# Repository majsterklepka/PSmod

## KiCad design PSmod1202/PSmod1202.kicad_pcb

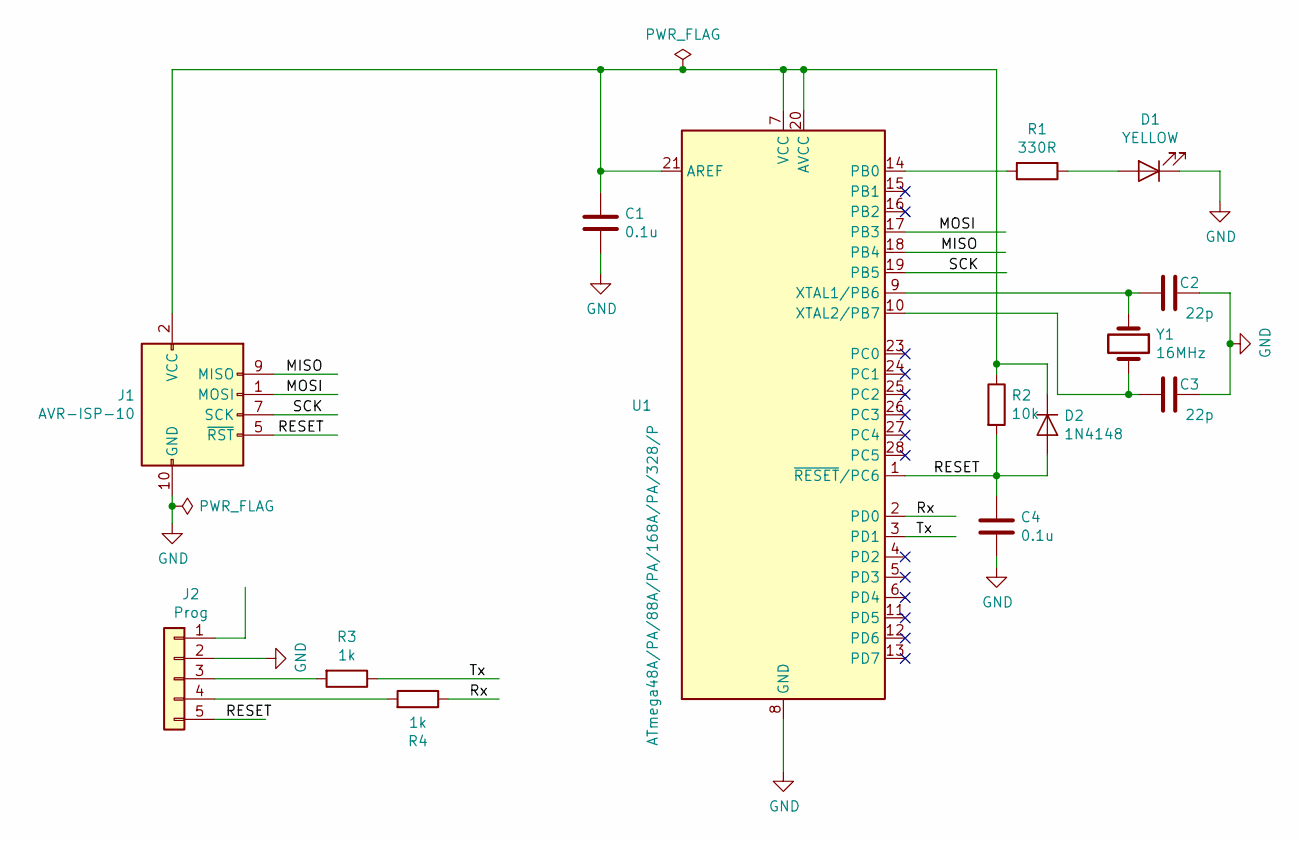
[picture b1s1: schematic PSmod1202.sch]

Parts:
C1, C4: 0.1u; C_Rect_L7.0mm_W2.0mm_P5.00mm
C2, C3: 22p; C_Disc_D4.3mm_W1.9mm_P5.00mm
D1: YELLOW; LED_D3.0mm
D2: 1N4148; D_DO-35_SOD27_P7.62mm_Horizontal
J1: AVR-ISP-10; IDC-Header_2x05_P2.54mm_Vertical
J2: Prog; PinHeader_1x05_P2.54mm_Vertical
R1: 330R; R_Axial_DIN0207_L6.3mm_D2.5mm_P7.62mm_Horizontal
R2: 10k; R_Axial_DIN0207_L6.3mm_D2.5mm_P7.62mm_Horizontal
R3, R4: 1k; R_Axial_DIN0207_L6.3mm_D2.5mm_P7.62mm_Horizontal
U1: ATmega48A/PA/88A/PA/168A/PA/328/P; DIP_Socket-28_W6.9_W7.62_W10.16_W12.7_W13.5_3M_228-4817-00-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
Y1: 16MHz; Crystal_HC49-U_Vertical

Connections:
/MISO: J1.9 (MISO), U1.18 (PB4)
/MOSI: J1.1 (MOSI), U1.17 (PB3)
/RESET: C4.1, D2.2 (A), J1.5 (~RST), J2.5, R2.2, U1.1 (~RESET~/PC6)
/Rx: R4.1, U1.2 (PD0)
/SCK: J1.7 (SCK), U1.19 (PB5)
/Tx: R3.1, U1.3 (PD1)
GND: C1.2, C2.1, C3.1, C4.2, D1.1 (K), J1.4 (GND), J1.6 (GND), J1.8 (GND), J1.10 (GND), J2.2, U1.8 (GND), U1.22 (GND)
unnamed: C1.1, D2.1 (K), J1.2 (VCC), R2.1, U1.7 (VCC), U1.20 (AVCC), U1.21 (AREF)
unnamed: C2.2, U1.9 (XTAL1/PB6), Y1.1
unnamed: C3.2, U1.10 (XTAL2/PB7), Y1.2
unnamed: D1.2 (A), R1.1
unnamed: J2.3, R3.2
unnamed: J2.4, R4.2
unnamed: R1.2, U1.14 (PB0)

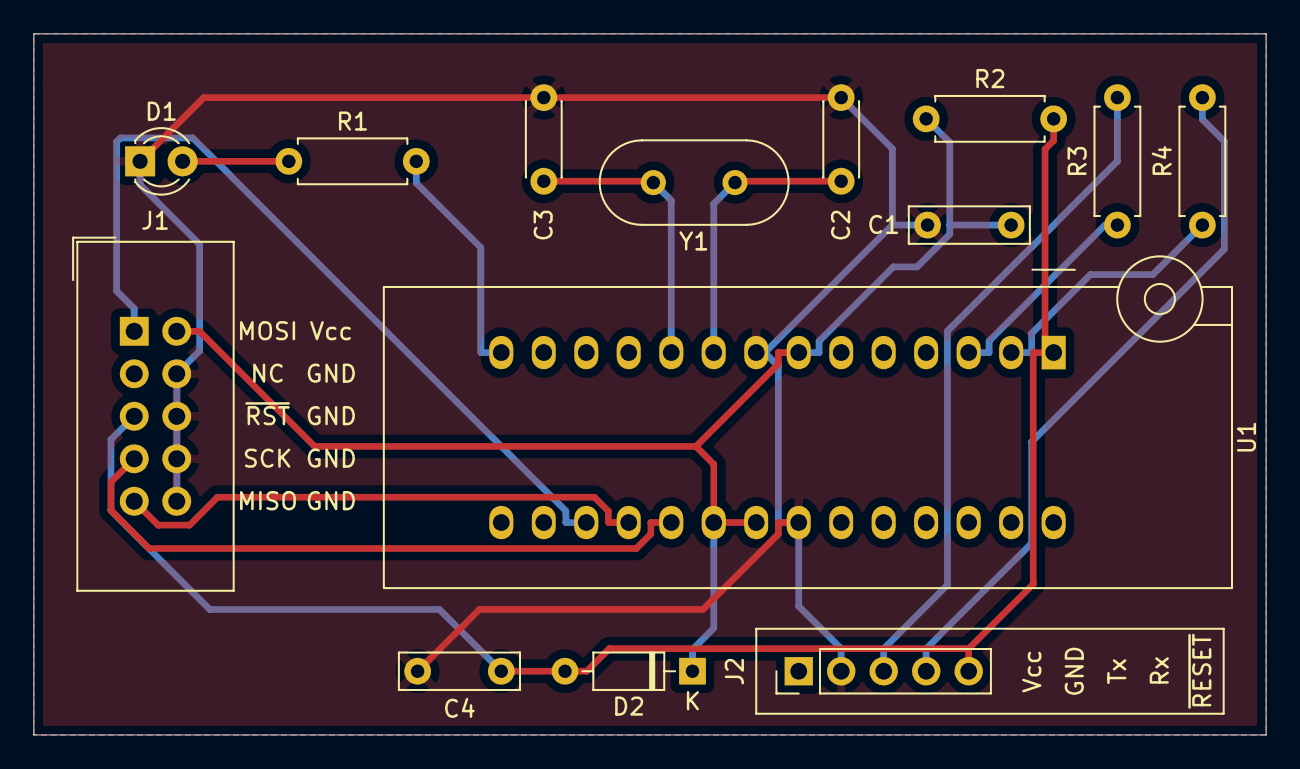
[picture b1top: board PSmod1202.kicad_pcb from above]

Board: 2 copper layers, 73.7 x 41.9 mm, 14 parts (0 on the bottom side), 14 nets.

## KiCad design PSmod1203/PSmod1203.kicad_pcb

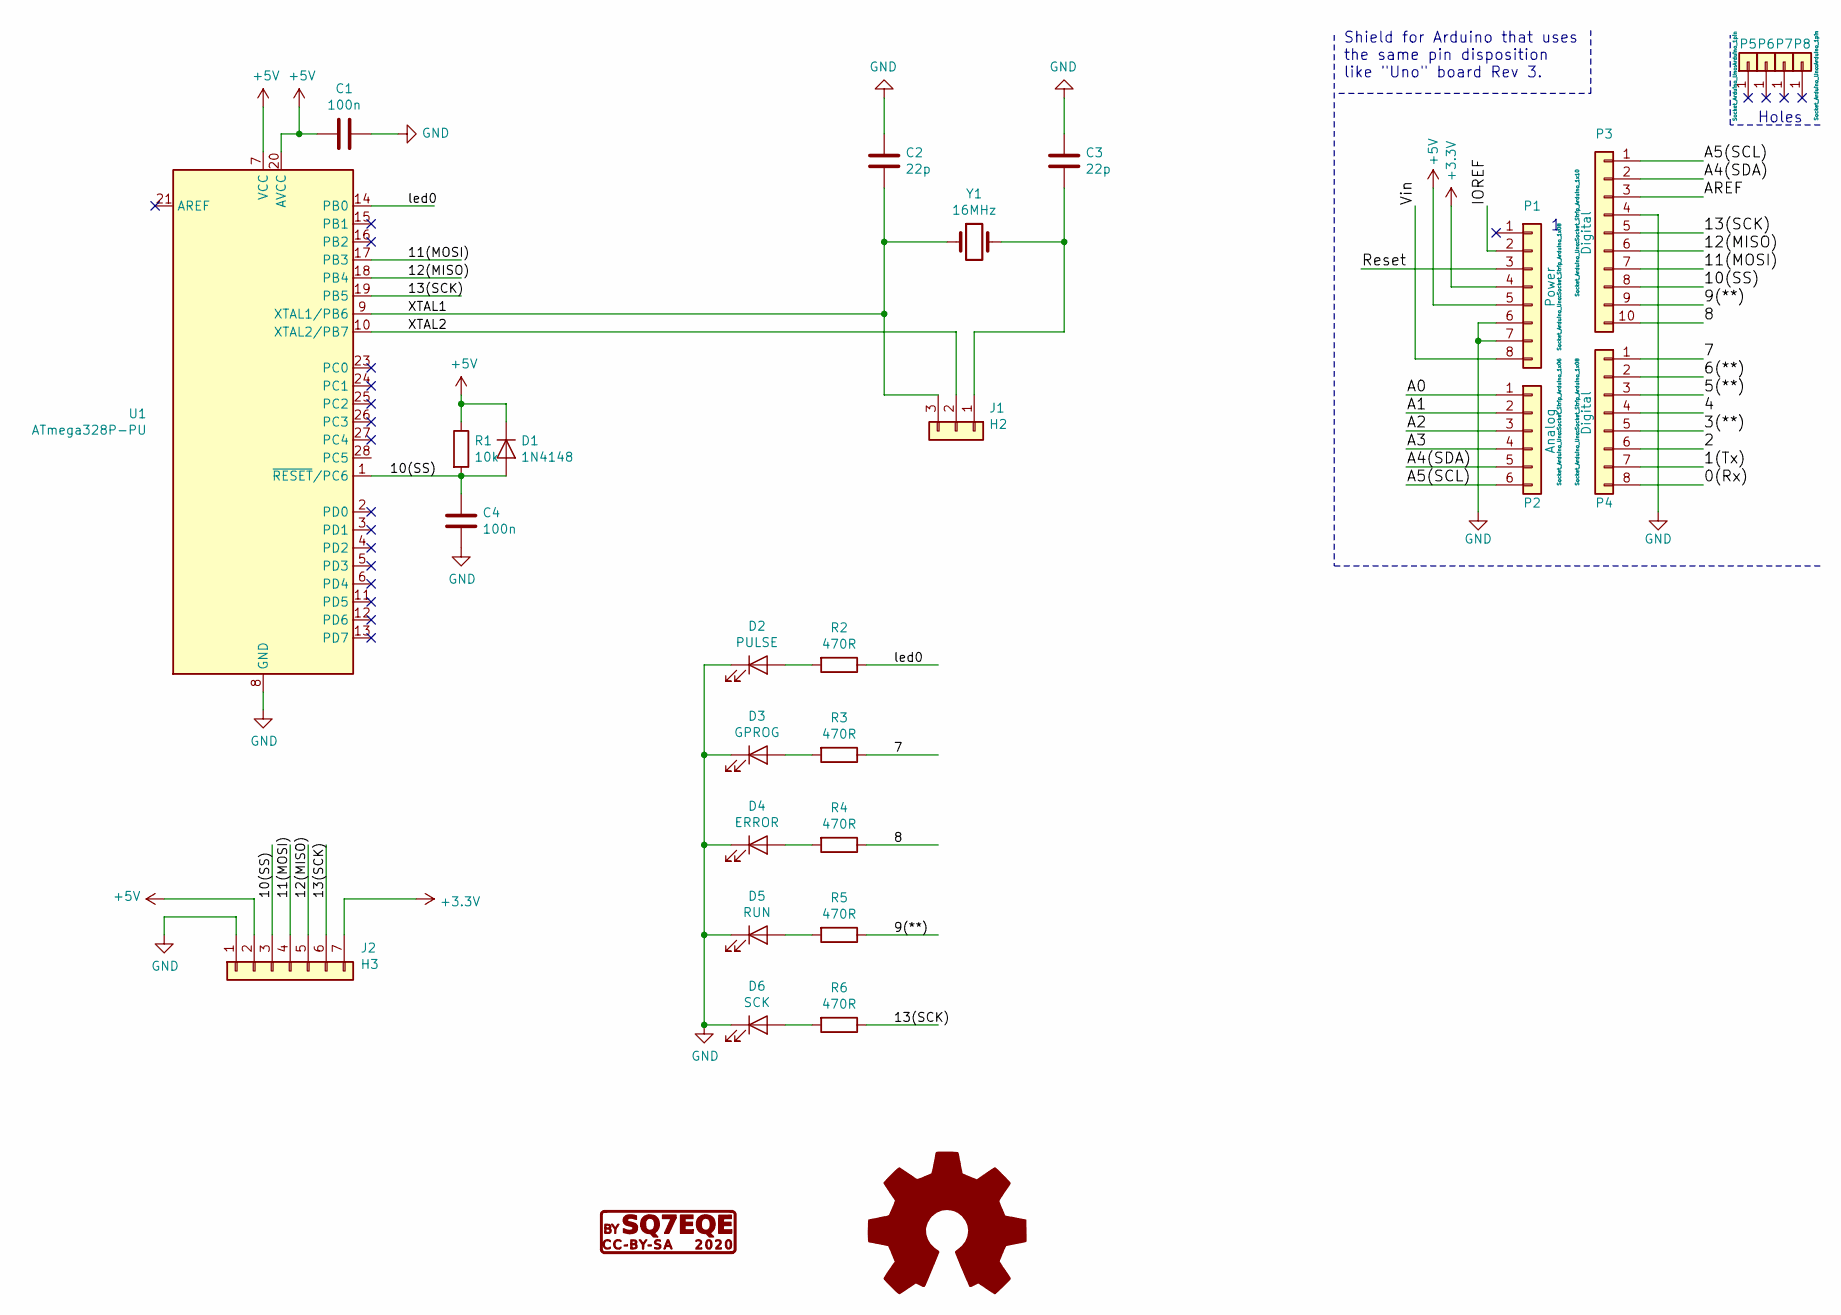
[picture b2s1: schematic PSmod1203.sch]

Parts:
C1, C4: 100n; C_Rect_L7.0mm_W2.0mm_P5.00mm
C2, C3: 22p; C_Disc_D4.3mm_W1.9mm_P5.00mm
D1: 1N4148; D_DO-35_SOD27_P7.62mm_Horizontal
D2: PULSE; LED_D3.0mm
D3: GPROG; LED_D3.0mm
D4: ERROR; LED_D3.0mm
D5: RUN; LED_D3.0mm
D6: SCK; LED_D3.0mm
G1: CC-BY-SA; cc-by-sa
J1: H2; PinHeader_1x03_P2.54mm_Vertical
J2: H3; PinHeader_1x07_P2.54mm_Vertical
LOGO1: Logo_Open_Hardware_Large; OSHW-Logo2_9.8x8mm_SilkScreen
P1: Power; Socket_Strip_Arduino_1x08
P2: Analog; Socket_Strip_Arduino_1x06
P3: Digital; Socket_Strip_Arduino_1x10
P4: Digital; Socket_Strip_Arduino_1x08
P5, P6, P7, P8: CONN_01X01; Arduino_1pin
R1: 10k; R_Axial_DIN0207_L6.3mm_D2.5mm_P7.62mm_Horizontal
R2, R3, R4, R5, R6: 470R; R_Axial_DIN0207_L6.3mm_D2.5mm_P7.62mm_Horizontal
U1: ATmega328P-PU; DIP_Socket-28_W6.9_W7.62_W10.16_W12.7_W13.5_3M_228-4817-00-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
Y1: 16MHz; Crystal_HC49-4H_Vertical

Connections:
+3V3: J2.7, P1.4
+5V: C1.2, D1.1 (K), J2.2, P1.5, R1.1, U1.7 (VCC), U1.20 (AVCC)
/0(Rx): P4.8
/1(Tx): P4.7
/2: P4.6
/3(**): P4.5
/4: P4.4
/5(**): P4.3
/6(**): P4.2
/7: P4.1, R3.1
/8: P3.10, R4.1
/9(**): P3.9, R5.1
/10(SS): C4.1, D1.2 (A), J2.3, P3.8, R1.2, U1.1 (~RESET~/PC6)
/11(MOSI): J2.4, P3.7, U1.17 (PB3)
/12(MISO): J2.5, P3.6, U1.18 (PB4)
/13(SCK): J2.6, P3.5, R6.1, U1.19 (PB5)
/A0: P2.1
/A1: P2.2
/A2: P2.3
/A3: P2.4
/A4(SDA): P2.5, P3.2
/A5(SCL): P2.6, P3.1
/AREF: P3.3
/IOREF: P1.2
/Reset: P1.3
/Vin: P1.8
/XTAL1: C2.2, J1.3, U1.9 (XTAL1/PB6), Y1.1
/XTAL2: J1.2, U1.10 (XTAL2/PB7)
/led0: R2.1, U1.14 (PB0)
GND: C1.1, C2.1, C3.1, C4.2, D2.1 (K), D3.1 (K), D4.1 (K), D5.1 (K), D6.1 (K), J2.1, P1.6, P1.7, P3.4, U1.8 (GND), U1.22 (GND)
unnamed: C3.2, J1.1, Y1.2
unnamed: D2.2 (A), R2.2
unnamed: D3.2 (A), R3.2
unnamed: D4.2 (A), R4.2
unnamed: D5.2 (A), R5.2
unnamed: D6.2 (A), R6.2

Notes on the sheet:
Holes
Shield for Arduino that uses the same pin disposition like "Uno" board Rev 3.

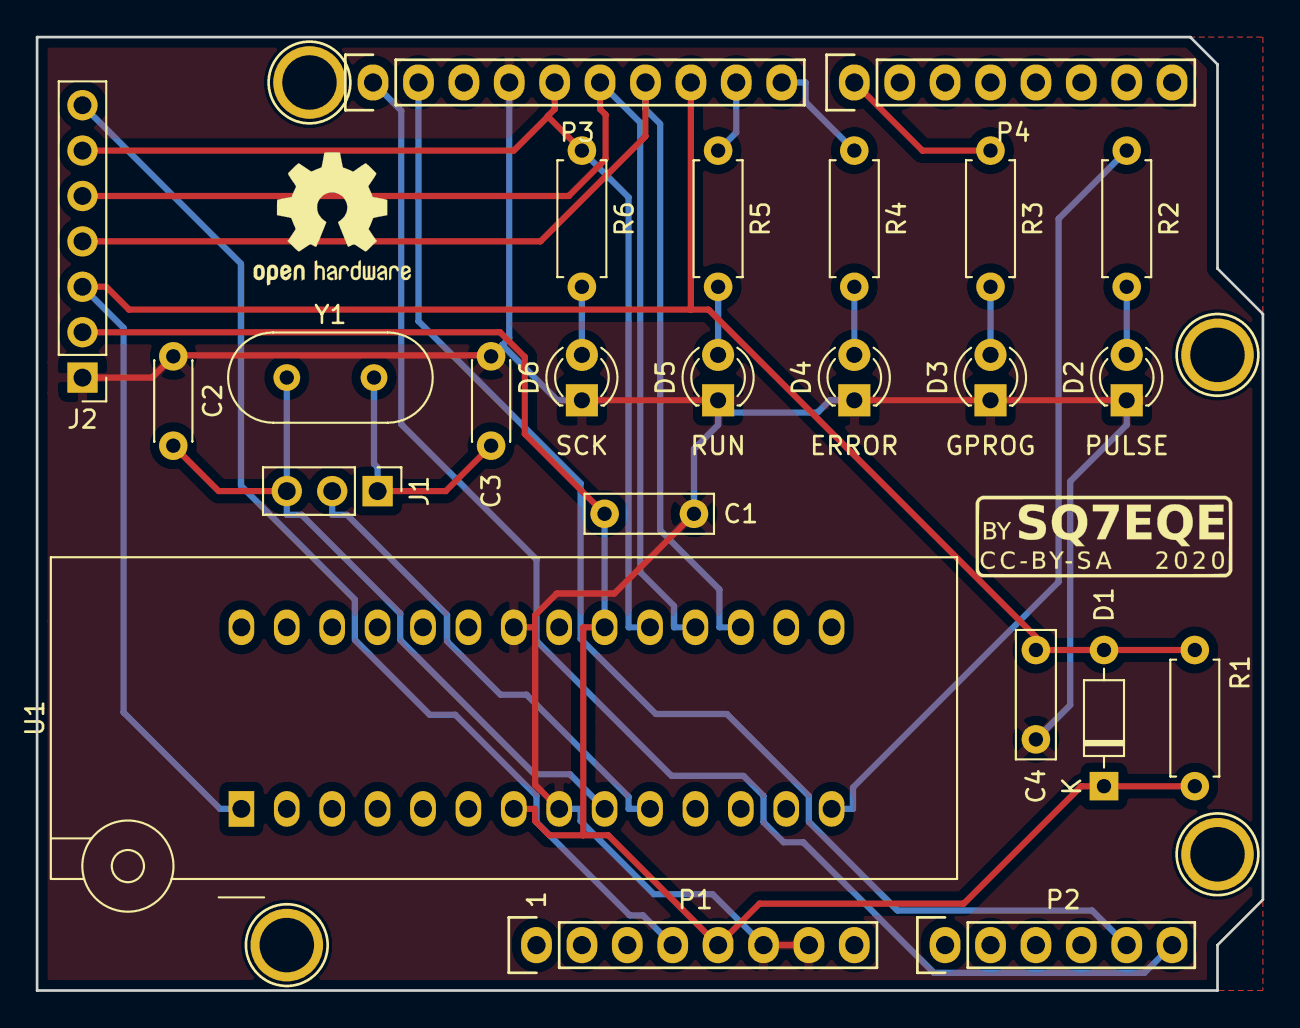
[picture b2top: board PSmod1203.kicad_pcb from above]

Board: 2 copper layers, 68.6 x 53.3 mm, 30 parts (0 on the bottom side), 21 nets.

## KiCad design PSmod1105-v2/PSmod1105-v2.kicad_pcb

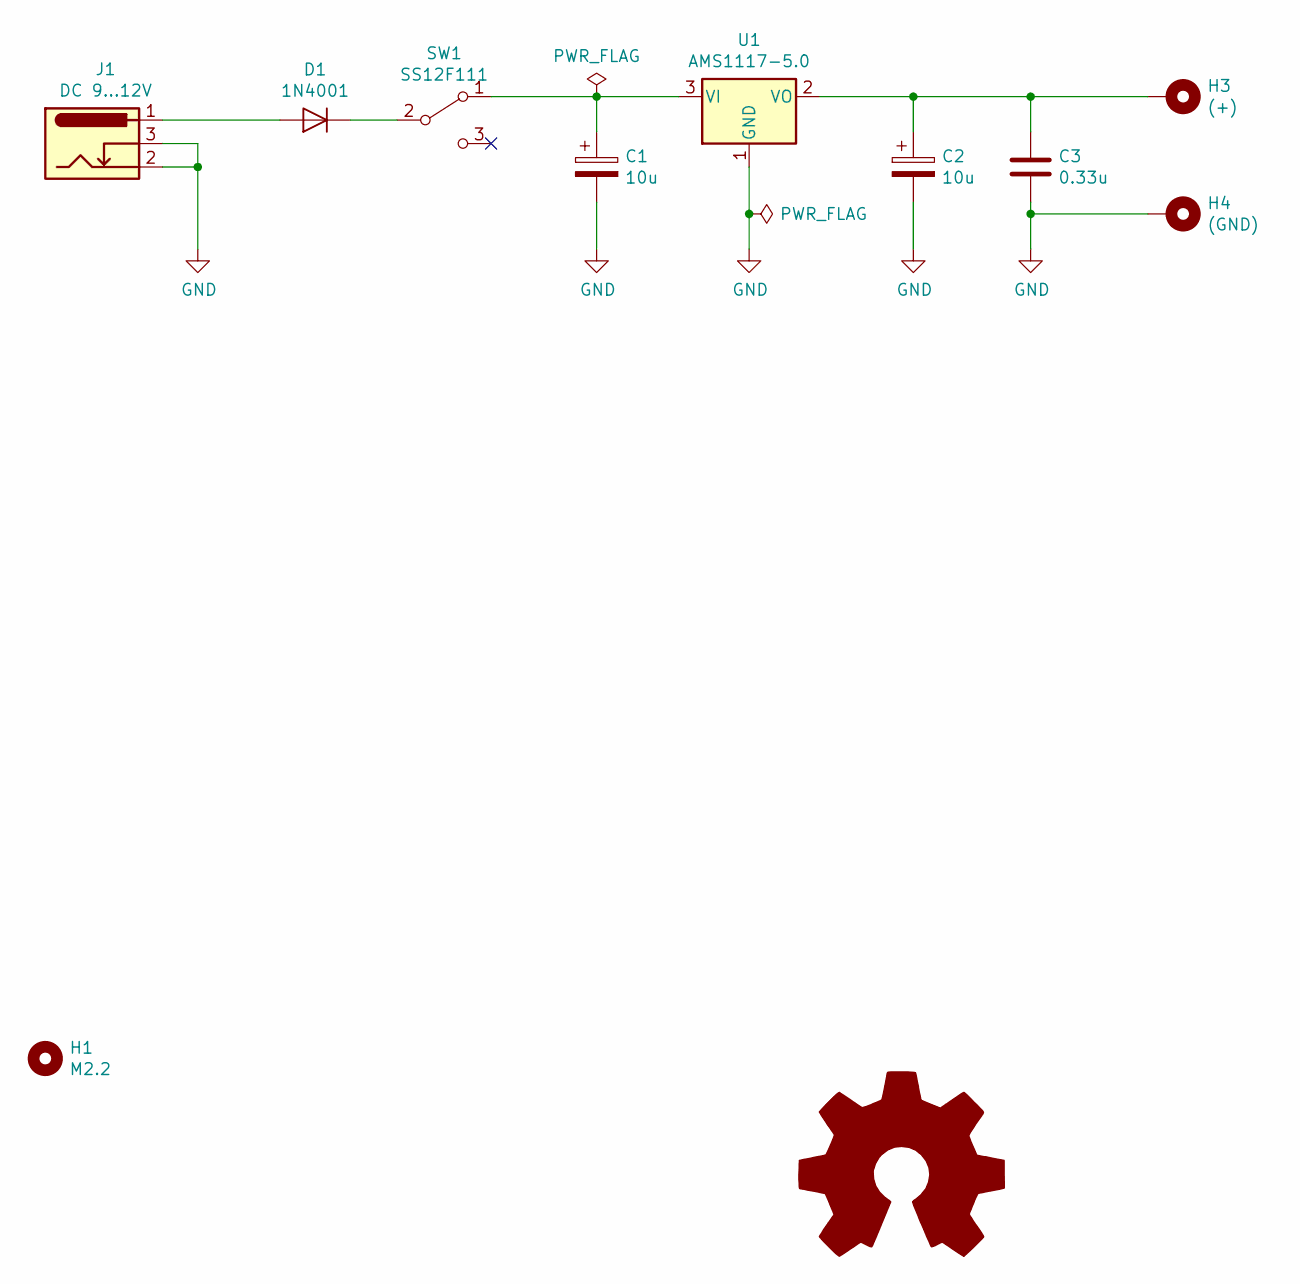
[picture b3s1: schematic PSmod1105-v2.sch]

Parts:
C1, C2: 10u; CP_Radial_D5.0mm_P2.50mm
C3: 0.33u; C_Rect_L7.0mm_W2.0mm_P5.00mm
D1: 1N4001; D_DO-41_SOD81_P10.16mm_Horizontal
H1: M2.2; MountingHole_2.2mm_M2_DIN965
H3: (+); MountingHole_2.2mm_M2_DIN965_Pad
H4: (GND); MountingHole_2.2mm_M2_DIN965_Pad
J1: DC 9...12V; NRB21R
LOGO1: Logo_Open_Hardware_Large; OSHW-Logo2_9.8x8mm_SilkScreen
SW1: SS12F111
U1: AMS1117-5.0; SOT-223-3_TabPin2

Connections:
GND: C1.2, C2.2, C3.2, H4.1, J1.2, J1.3, U1.1 (GND)
unnamed: C1.1, SW1.1 (A), U1.3 (VI)
unnamed: C2.1, C3.1, H3.1, U1.2 (VO)
unnamed: D1.1 (K), SW1.2 (B)
unnamed: D1.2 (A), J1.1

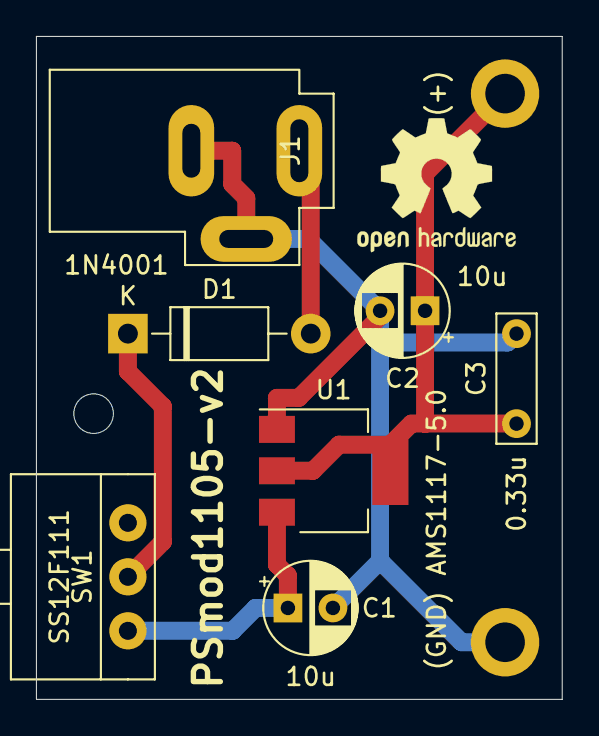
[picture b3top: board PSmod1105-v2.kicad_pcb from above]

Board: 2 copper layers, 29.2 x 36.8 mm, 11 parts (0 on the bottom side), 5 nets.

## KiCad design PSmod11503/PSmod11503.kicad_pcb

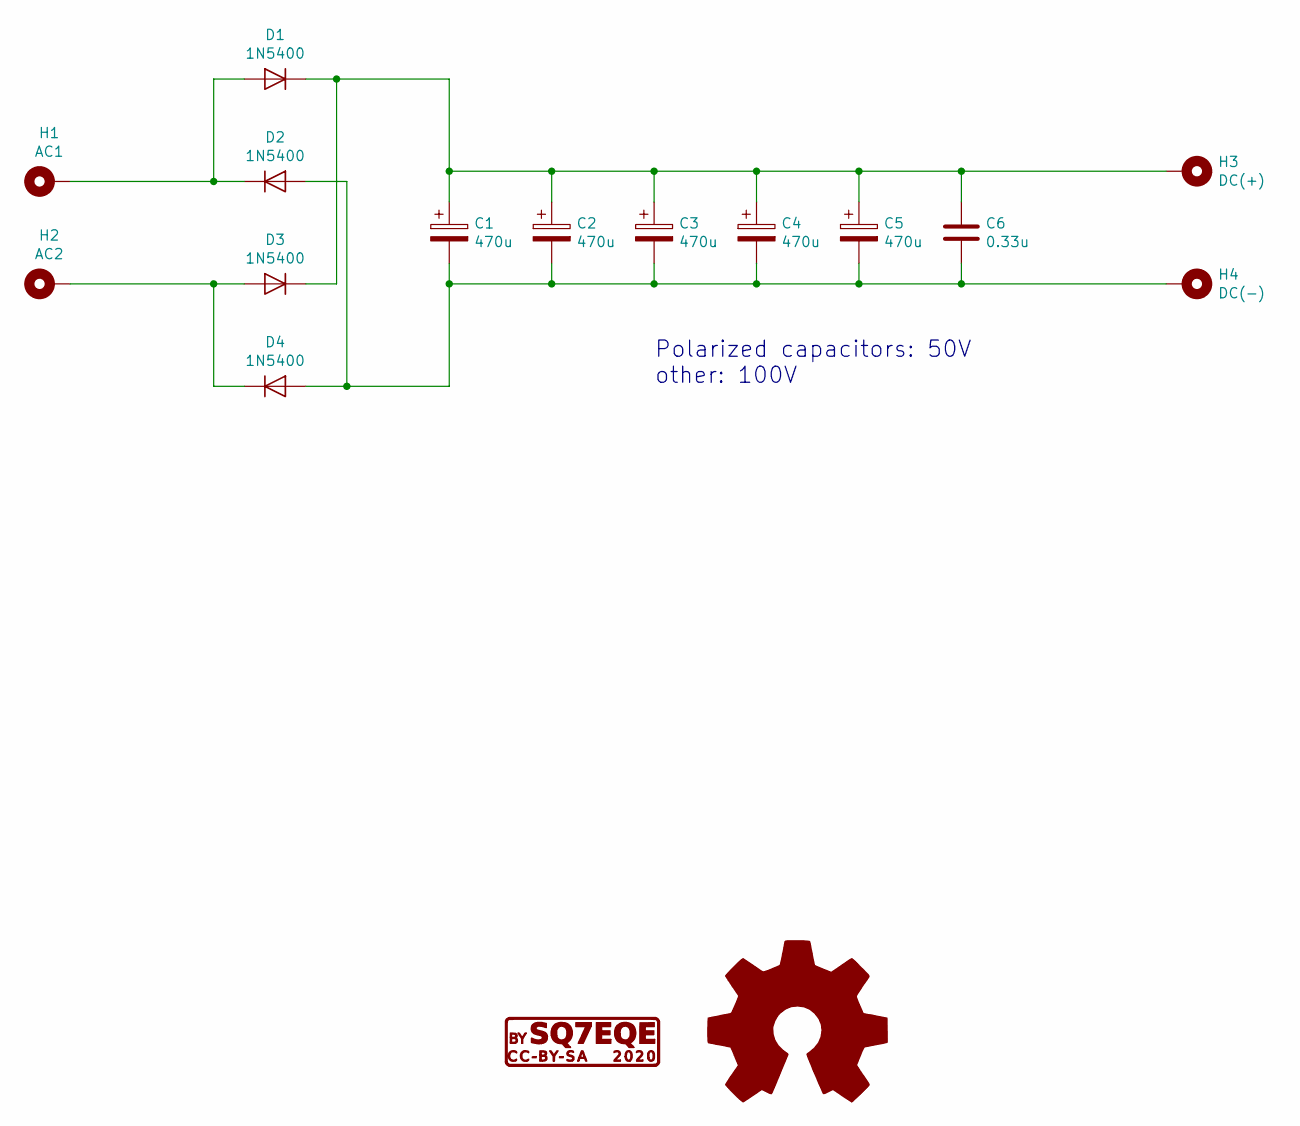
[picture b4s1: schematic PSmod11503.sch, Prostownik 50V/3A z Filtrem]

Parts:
C1, C2, C3, C4, C5: 470u; CP_Radial_D10.0mm_P5.00mm
C6: 0.33u; C_Rect_L7.0mm_W4.5mm_P5.00mm
D1, D2, D3, D4: 1N5400; D_DO-201AD_P15.24mm_Horizontal
G1: CC-BY-SA; cc-by-sa
G2: Logo_Open_Hardware_Large; OSHW-Logo2_14.6x12mm_SilkScreen
H1: AC1; MountingHole_3.2mm_M3_DIN965_Pad
H2: AC2; MountingHole_3.2mm_M3_DIN965_Pad
H3: DC(+); MountingHole_3.2mm_M3_DIN965_Pad
H4: DC(-); MountingHole_3.2mm_M3_DIN965_Pad

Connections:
unnamed: C1.1, C2.1, C3.1, C4.1, C5.1, C6.1, D1.1 (K), D3.1 (K), H3.1
unnamed: C1.2, C2.2, C3.2, C4.2, C5.2, C6.2, D2.2 (A), D4.2 (A), H4.1
unnamed: D1.2 (A), D2.1 (K), H1.1
unnamed: D3.2 (A), D4.1 (K), H2.1

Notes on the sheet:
Polarized capacitors: 50V other: 100V

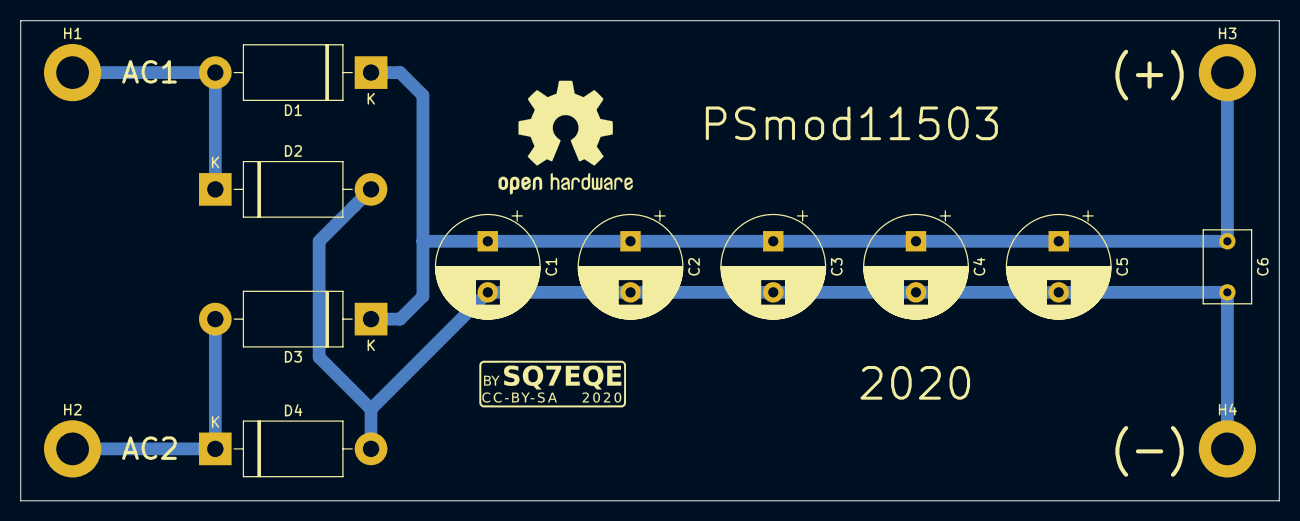
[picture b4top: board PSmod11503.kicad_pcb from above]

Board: 2 copper layers, 123.2 x 47.0 mm, 16 parts (0 on the bottom side), 4 nets.

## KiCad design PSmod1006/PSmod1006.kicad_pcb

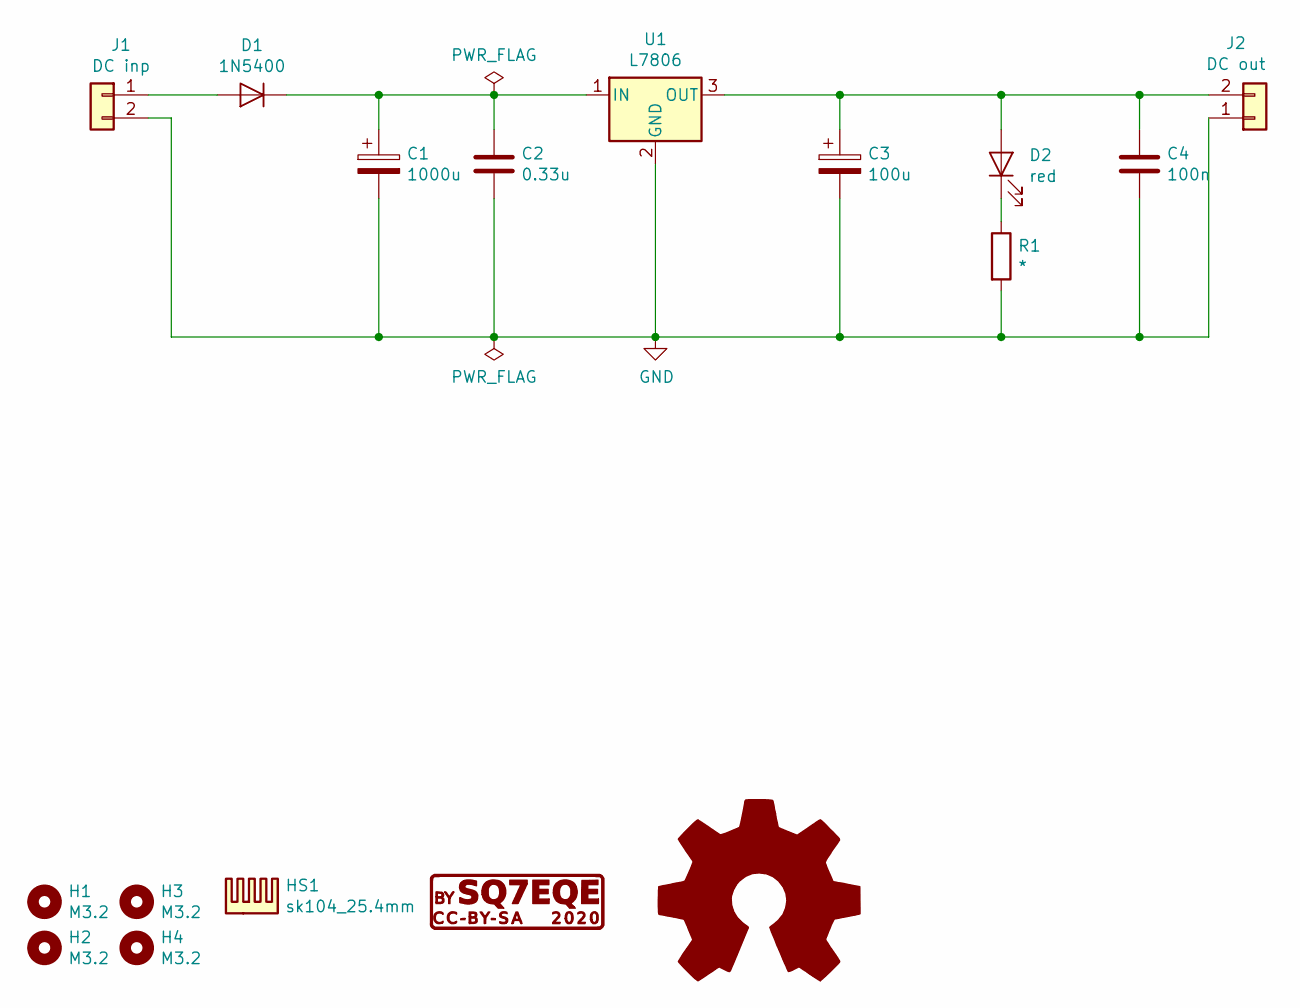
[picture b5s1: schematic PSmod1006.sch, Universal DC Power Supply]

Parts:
C1: 1000u; CP_Radial_D10.0mm_P5.00mm
C2: 0.33u; C_Rect_L7.0mm_W2.5mm_P5.00mm
C3: 100u; CP_Radial_D6.3mm_P2.50mm
C4: 100n; C_Rect_L7.0mm_W2.5mm_P5.00mm
D1: 1N5400; D_DO-201AD_P15.24mm_Horizontal
D2: red; LED_D5.0mm
G1: CC-BY-SA; cc-by-sa
G2: Logo_Open_Hardware_Large; OSHW-Logo2_14.6x12mm_SilkScreen
H1, H2, H3, H4: M3.2; MountingHole_3.2mm_M3
HS1: sk104_25.4mm
J1: DC inp; DG301-5.0-2P
J2: DC out; DG301-5.0-2P
R1: *; R_Axial_DIN0204_L3.6mm_D1.6mm_P7.62mm_Horizontal
U1: L7806; TO-220-3_Vertical

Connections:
GND: C1.2, C2.2, C3.2, C4.2, J1.2, J2.1, R1.2, U1.2 (GND)
unnamed: C1.1, C2.1, D1.1 (K), U1.1 (IN)
unnamed: C3.1, C4.1, D2.2 (A), J2.2, U1.3 (OUT)
unnamed: D1.2 (A), J1.1
unnamed: D2.1 (K), R1.1

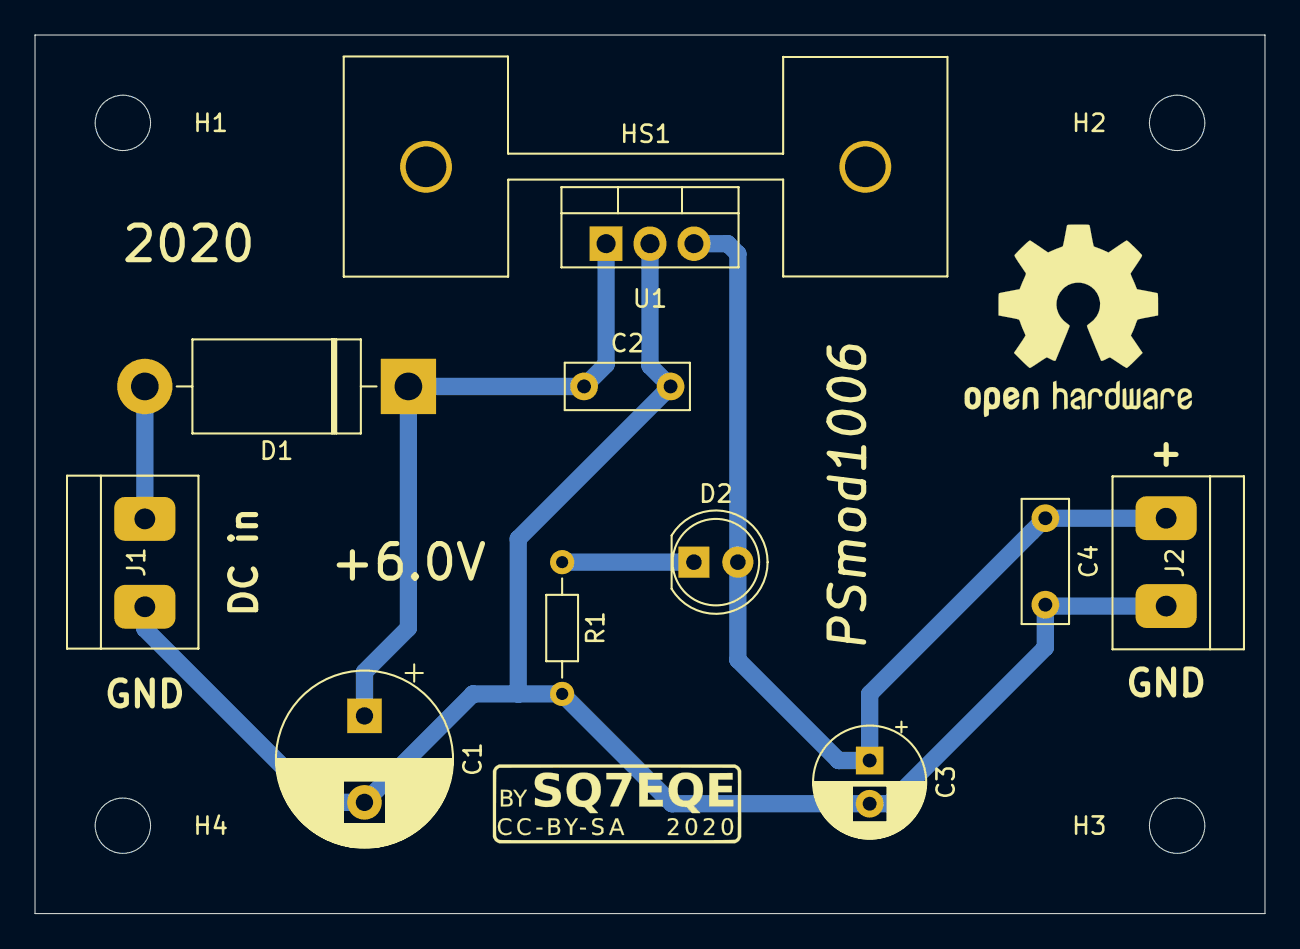
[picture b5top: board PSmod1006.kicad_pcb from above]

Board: 2 copper layers, 71.1 x 50.8 mm, 17 parts (0 on the bottom side), 5 nets.

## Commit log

2020-10-30 Create LICENSE
2020-10-30 new project
2020-11-02 new module project
2020-12-29 new module

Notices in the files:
PSmod1006/PSmod1006.kicad_pcb:
CC-BY-SA 4.0
